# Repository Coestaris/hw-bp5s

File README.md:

# BP5S - five-cell battery protector

> **AI use.** The authors use AI for additional validation, component research, testbench setup and simulation, intermediate design reviews, release setup, and assistance with KiCad and 3D model edits. The authors developed the original designs and schematics manually, and other people reviewed them. The authors make the technical and visual decisions and take responsibility for them.

Project has been manufactured and tested at real hardware.
BP5S provides a dedicated protection board for a five-series-cell battery pack, but not a charging or any kind of switching cictuit.

## Nominal characteristics

| Characteristic | Rev1 design value |
| --- | --- |
| Battery configuration | 5 series Li-ion cells, 18.0–18.5 V nominal at 3.6–3.7 V per cell |
| Cell overvoltage and undervoltage trips | 4.20 V and 2.90 V per cell, respectively, with a nominal 1 s detection delay |
| Charge overcurrent trip | 6 A nominal, 10 ms detection delay |
| Discharge overcurrent trip | 6 A nominal, 180 ms detection delay |
| Discharge short-circuit trip | 12 A nominal, 960 µs detection delay |
| Temperature sensing | External 10 kΩ NTC on TH1. With a 103AT thermistor, nominal low/high trips are 0 °C / 45 °C for charge and −10 °C / 65 °C for discharge |
| Cell balancing | Passive balancing during charge, with a 3.80 V per-cell start threshold and a 50 mA limit for the controller’s internal balancing path |
| Connections | BATT− and BATT+ pads, four intermediate cell taps on J3, and an XT60 pack connector on J6 |

## Goals and architecture

Keep cell monitoring and pack protection on a compact board, with a thermistor input and a high-current pack connection. The BQ7791500PWR monitors the cell stack and controls two CSD18534Q5A power MOSFETs. Input filtering, transient protection, and the temperature-sense network support the protection stage; the pack connection uses an XT60 connector.

```mermaid
flowchart LR
  Cells[5S cell stack] --> Monitor[BQ77915 protection controller]
  Temperature[Thermistor] --> Monitor
  Monitor --> Switches[Power MOSFET pair]
  Cells --> Switches --> Pack[Pack connector]
```

## rev1

Rev1 has been manufactured and tested at real hardware [Rev1 release](https://github.com/Coestaris/hw-bp5s/releases/tag/rev1)

<details>
<summary>Top and bottom views</summary>

</details>

| File | Download |
| --- | --- |
| Schematic PDF | [bp5s-schematic.pdf](https://github.com/Coestaris/hw-bp5s/releases/download/rev1/bp5s-schematic.pdf) |
| PCB PDF | [bp5s-pcb.pdf](https://github.com/Coestaris/hw-bp5s/releases/download/rev1/bp5s-pcb.pdf) |
| Gerbers and drill files | [bp5s-gerbers.zip](https://github.com/Coestaris/hw-bp5s/releases/download/rev1/bp5s-gerbers.zip) |
| JLCPCB BOM | [bp5s-jlcpcb-bom.csv](https://github.com/Coestaris/hw-bp5s/releases/download/rev1/bp5s-jlcpcb-bom.csv) |
| JLCPCB placement | [bp5s-jlcpcb-pnp.csv](https://github.com/Coestaris/hw-bp5s/releases/download/rev1/bp5s-jlcpcb-pnp.csv) |
| 3D assembly model | [bp5s.stpz](https://github.com/Coestaris/hw-bp5s/releases/download/rev1/bp5s.stpz) |

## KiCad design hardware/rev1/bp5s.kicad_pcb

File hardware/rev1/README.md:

# BP5S revision 1

Manufactured five-series-cell battery protection board. The active design uses a BQ7791500PWR protection controller and a CSD18534Q5A power MOSFET pair, with cell-sense filtering, temperature sensing, and an XT60 pack connection.

Open [bp5s.kicad_pro](bp5s.kicad_pro) in KiCad 10. The local symbol and footprint libraries are included alongside the project; shared component models and datasheets are included in [assets](../../assets/).

See the [project overview](../../README.md) for architecture and release downloads, and the [test plan](test-plan.html) for bring-up checks.

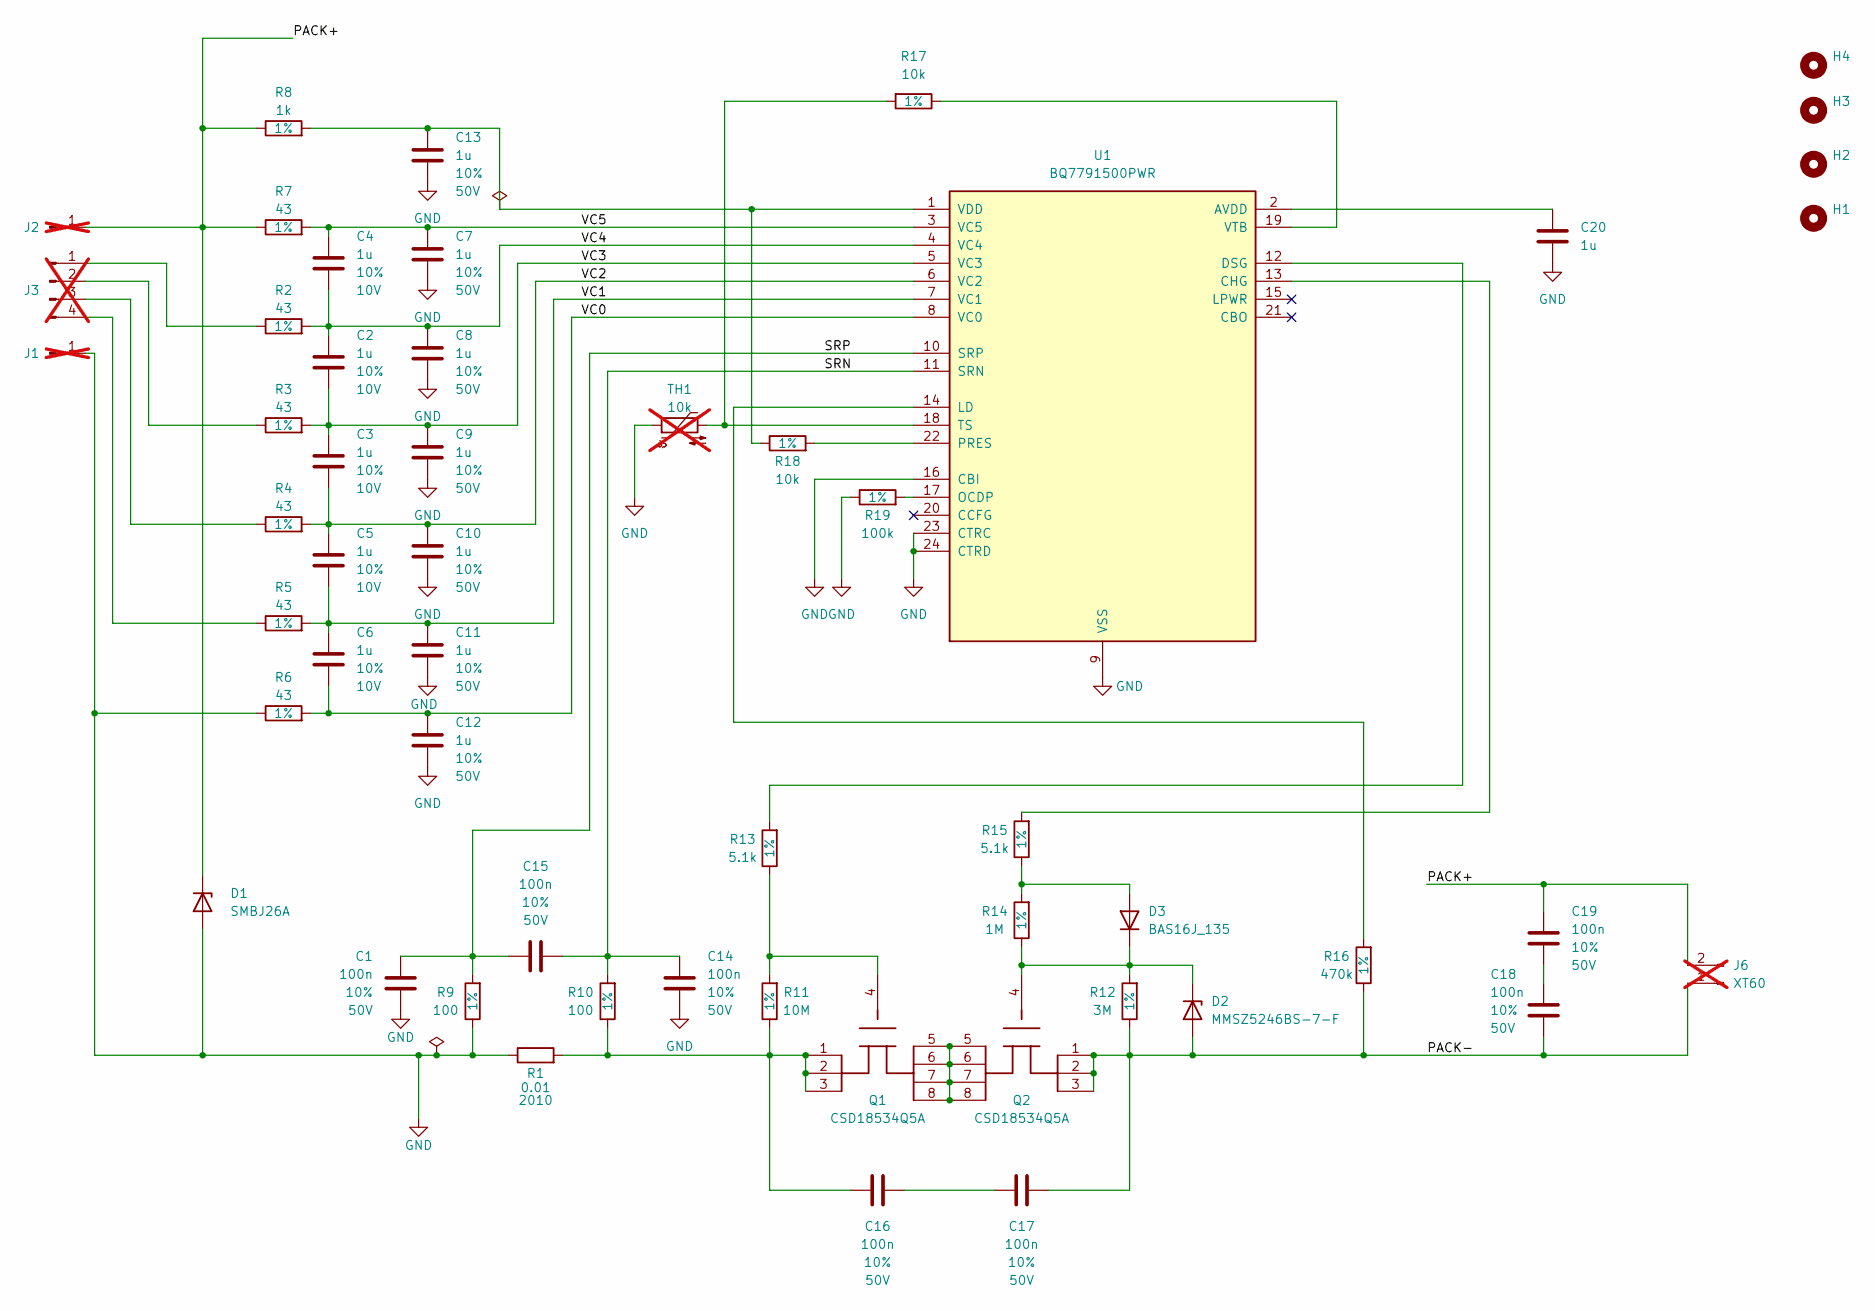
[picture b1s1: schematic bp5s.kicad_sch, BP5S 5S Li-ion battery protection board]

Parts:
C1, C14, C15, C16, C17, C18, C19: 100n; C_0805_2012Metric; Tolerance 10%; Voltage 50V; Manufacturer Part Number CC0805KRX7R9BB104; JLCPCB Part Type Basic
C2, C3, C4, C5, C6, C20: 1u; C_0805_2012Metric; Tolerance 10%; Voltage 10V; Manufacturer Part Number C0805C105K8RACTU; JLCPCB Part Type Extended
C7, C8, C9, C10, C11, C12, C13: 1u; C_0805_2012Metric; Tolerance 10%; Voltage 50V; Manufacturer Part Number CL21B105KBFNNNE; JLCPCB Part Type Basic
D1: SMBJ26A; D_SMB; Manufacturer Part Number SMBJ26A; LCSC C315992
D2: MMSZ5246BS-7-F; D_SOD-323; Manufacturer Part Number MMSZ5246BS-7-F; LCSC C151819
D3: BAS16J_135; D_SOD-323F; Manufacturer Part Number BAS16J,135; LCSC C549198
H1, H2, H3, H4: MountingHole; MountingHole_3.2mm_M3_ISO14580
J1, J2: Conn_01x01_Pin; TestPoint_THTPad_4.0x4.0mm_Drill2.0mm; not fitted
J3: Conn_01x04_Pin; Molex_KK-254_AE-6410-04A_1x04_P2.54mm_Vertical; not fitted
J6: XT60; AMASS_XT60-F_1x02_P7.20mm_Vertical; not fitted
Q1, Q2: CSD18534Q5A; Texas_Q5A_CSD18534; Manufacturer Part Number CSD18534Q5A; LCSC C115943
R1: 0.01; R_2010_5025Metric; MPN CSRN2010FT10L0; LCSC C346837
R2, R3, R4, R5, R6, R7: 43; R_1206_3216Metric; Tolerance 1%; Manufacturer Part Number 1RC1206F4309; JLCPCB Part Type Extended
R8: 1k; R_0805_2012Metric; Tolerance 1%; Manufacturer Part Number 0805W8F1001T5E; JLCPCB Part Type Basic
R9, R10: 100; R_0805_2012Metric; Tolerance 1%; Manufacturer Part Number 0805W8F1000T5E; JLCPCB Part Type Basic
R11: 10M; R_0805_2012Metric; Tolerance 1%; Manufacturer Part Number 0805W8F1005T5E; JLCPCB Part Type Promotional Extended
R12: 3M; R_0805_2012Metric; Tolerance 1%; Manufacturer Part Number 0805W8F3004T5E; JLCPCB Part Type Extended
R13, R15: 5.1k; R_0805_2012Metric; Tolerance 1%; Manufacturer Part Number 0805W8F5101T5E; JLCPCB Part Type Basic
R14: 1M; R_0805_2012Metric; Tolerance 1%; Manufacturer Part Number 0805W8F1004T5E; JLCPCB Part Type Basic
R16: 470k; R_0805_2012Metric; Tolerance 1%; Manufacturer Part Number 0805W8F4703T5E; JLCPCB Part Type Basic
R17, R18: 10k; R_0805_2012Metric; Tolerance 1%; Manufacturer Part Number 0805W8F1002T5E; JLCPCB Part Type Basic
R19: 100k; R_0805_2012Metric; Tolerance 1%; Manufacturer Part Number 0805W8F1003T5E; JLCPCB Part Type Basic
TH1: 10k; PinHeader_1x02_P2.54mm_Vertical; not fitted
U1: BQ7791500PWR; TSSOP-24_4.4x7.8mm_P0.65mm; Manufacturer Part Number BQ7791500PWR; LCSC C2876946

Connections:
/PACK+: C19.1, D1.1 (K), J2.1 (Pin_1_1), J6.2, R7.1, R8.1
/PACK-: C17.1, C18.2, D2.2 (A), J6.1, Q2.1 (S), Q2.2 (S), Q2.3 (S), R12.1, R16.1
/SRN: C14.2, C15.2, R10.2, U1.11 (SRN)
/SRP: C1.2, C15.1, R9.2, U1.10 (SRP)
/VC0: C6.1, C12.2, R6.2, U1.8 (VC0)
/VC1: C5.1, C6.2, C11.2, R5.2, U1.7 (VC1)
/VC2: C3.1, C5.2, C10.2, R4.2, U1.6 (VC2)
/VC3: C2.1, C3.2, C9.2, R3.2, U1.5 (VC3)
/VC4: C2.2, C4.1, C8.2, R2.2, U1.4 (VC4)
/VC5: C4.2, C7.2, R7.2, U1.3 (VC5)
GND: C1.1, C7.1, C8.1, C9.1, C10.1, C11.1, C12.1, C13.1, C14.1, C20.1, D1.2 (A), J1.1 (Pin_1_1), R1.1, R6.1, R9.1, R19.1, TH1.1, U1.9 (VSS), U1.16 (CBI), U1.23 (CTRC), U1.24 (CTRD)
unnamed: C16.1, C17.2
unnamed: C16.2, Q1.1 (S), Q1.2 (S), Q1.3 (S), R1.2, R10.1, R11.1
unnamed: C18.1, C19.2
unnamed: D2.1 (K), D3.1 (K), Q2.4 (G), R12.2, R14.1
unnamed: D3.2 (A), R14.2, R15.1
unnamed: J3.1, R2.1
unnamed: J3.2, R3.1
unnamed: J3.3, R4.1
unnamed: J3.4, R5.1
unnamed: Q1.5 (D), Q1.6 (D), Q1.7 (D), Q1.8 (D), Q2.5 (D), Q2.6 (D), Q2.7 (D), Q2.8 (D)
unnamed: Q1.4 (G), R11.2, R13.1
unnamed: C20.2, U1.2 (AVDD)
unnamed: R15.2, U1.13 (CHG)
unnamed: R13.2, U1.12 (DSG)
unnamed: R16.2, U1.14 (LD)
unnamed: R19.2, U1.17 (OCDP)
unnamed: R18.2, U1.22 (PRES)
unnamed: R17.2, TH1.2, U1.18 (TS)
unnamed: C13.2, R8.2, R18.1, U1.1 (VDD)
unnamed: R17.1, U1.19 (VTB)

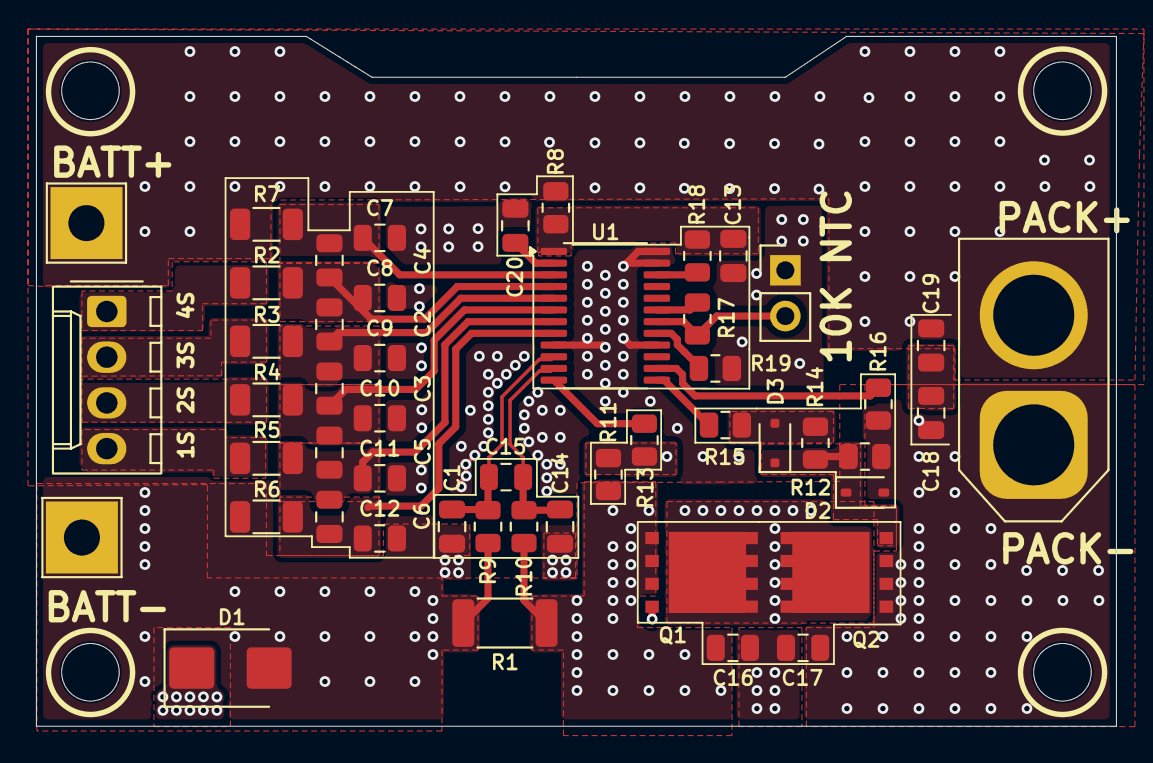
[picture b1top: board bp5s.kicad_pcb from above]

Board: 4 copper layers, 60.0 x 38.3 mm, 54 parts (0 on the bottom side), 31 nets.
